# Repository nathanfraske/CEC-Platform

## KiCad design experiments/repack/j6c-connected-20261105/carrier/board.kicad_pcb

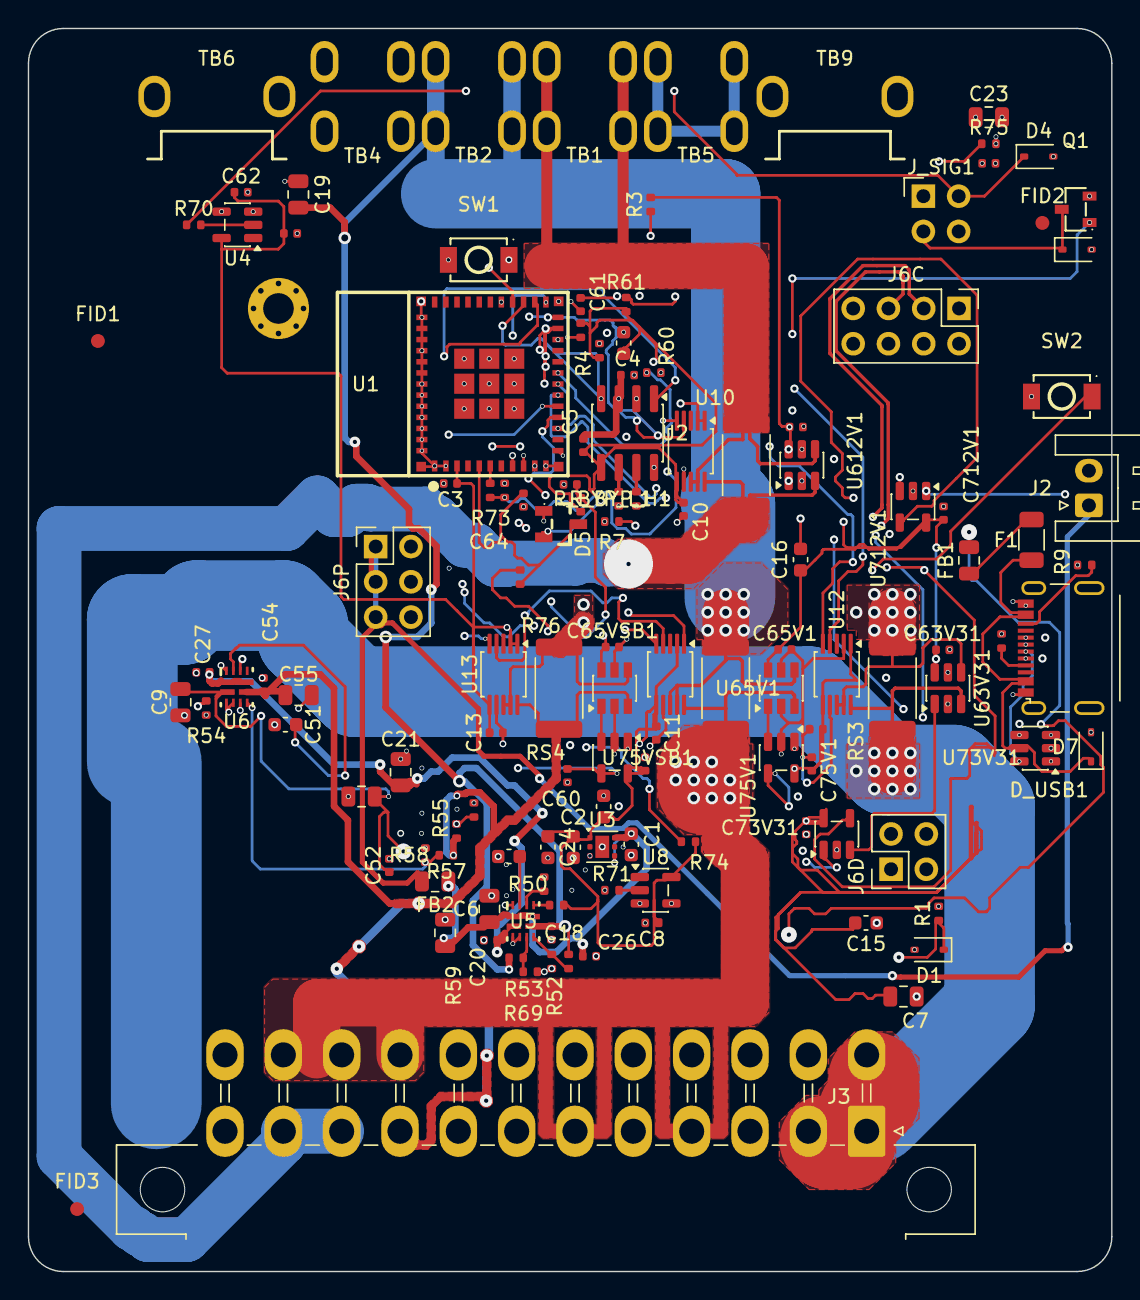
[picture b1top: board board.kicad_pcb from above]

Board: 6 copper layers, 78.0 x 89.5 mm, 129 parts (0 on the bottom side), 63 nets.

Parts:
C1, C2, C14, C15, C16, C17, C24: 1uF; C_0603_1608Metric
C3, C4, C5, C8, C10, C11, C12, C13, C18, C20, C22, C26, C27, C28, C52, C54, C60, C61, C62, C63, C63V31, C64, C65V1, C65VSB1, C73V31, C75V1, C75VSB1, C612V1, C712V1: 100nF; C_0402_1005Metric
C6, C7, C9, C19, C21, C23, C53, C55: 10uF; C_0805_2012Metric
C25: 22uF; C_0805_2012Metric
C50: 2u2; C_0603_1608Metric
C51: 2.2uF; C_0603_1608Metric
D1, D3, D4, D7: PESD5V0S1BA; D_SOD-323
D5: BAT54S; SOT-23-3_L2.9-W1.3-P1.90-LS2.4-TL
D_USB1: USBLC6-2SC6; SOT-23-6
F1: 750mA/16V PTC; R_1206_3216Metric
FB1: 600R@100MHz FB (MPZ2012S601AT000); C_0805_2012Metric
FB2: 0R (FB position, populate on EMC evidence); C_0805_2012Metric
FID1, FID2, FID3: Fiducial_1mm_Mask2mm
H1: M2 GND lug; MountingHole_2.2mm_M2_Pad_Via_Slim_6mm_Hardware
J2: TO-HUB-PWR; JST_XH_S2B-XH-A_1x02_P2.50mm_Horizontal
J3: ATX-24 PSU; Molex_Mini-Fit_Jr_5569-24A1_2x12_P4.20mm_Horizontal
J5: USB-C 2.0; USB_C_Receptacle_GCT_USB4215-03-A
J6C: TO-HUB-STACK-COMMS; PinHeader_2x04_P2.54mm_Vertical
J6D: TO-HUB-STACK-ID; PinHeader_2x02_P2.54mm_Vertical
J6P: TO-HUB-STACK-PWR; PinHeader_2x03_P2.54mm_Vertical
J_SIG1: SSQ-102-03-G-D; Samtec_SSQ-102-03-G-D_2x02_P2.54mm_Vertical
Q1: AO3400A; SOT-23-3_L2.9-W1.3-P1.90-LS2.4-BR
R1, R3, R4: 2.2kΩ; R_0402_1005Metric
R2, R10, R51, R56, R60, R61, R69, R76: 10kΩ; R_0402_1005Metric
R7, R52, R54, R57, R73, R75: 100kΩ; R_0402_1005Metric
R8, R9: 5.1kΩ; R_0402_1005Metric
R50: 20kΩ; R_0402_1005Metric
R53, R58: 33kΩ; R_0402_1005Metric
R55, R59: 43.2kΩ; R_0402_1005Metric
R70, R71: 1kΩ; R_0402_1005Metric
R72: 100Ω; R_0402_1005Metric
R74: 15kΩ; R_0402_1005Metric
RS1, RS2, RS3: 2mΩ; R_2512_6332Metric
RS4: R025; R_2512_6332Metric
R_BYP_H1: 0Ω; R_0402_1005Metric
R_BYP_L1: 0Ω; R_0402_1005Metric
SW1: BOOT; TS-1088-AR02016
SW2: RESET; TS-1088-AR02016
TB1, TB2, TB4, TB5: XFCN T34069; XFCN_T34069_THT_M3_40A
TB6, TB9: TTR32100127-0600; XFCN_TTR32100127-0600_THT_M3_60A
U1: ESP32-C6-MINI-1-N4; ESP32-C6-MINI-1
U2: TJA1051T/3; SOIC-8_3.9x4.9mm_P1.27mm
U3: TLV75533PDRVR; WSON-6-1EP_2x2mm_P0.65mm_EP1x1.6mm
U4, U8: 74LVC1G17; SOT-23-5
U5, U6: TPS2121RUXR; RUX0012A
U10, U11, U12, U13: INA238; VSSOP-10_3x3mm_P0.5mm
U63V31, U612V1: INA181A2IDBVR; SOT-23-6
U65V1, U65VSB1: INA181A2IDBVR; SOT-23-6_TI_DBV0006A
U73V31, U75V1, U75VSB1, U712V1: TLV7011DBVR; SOT-23-5

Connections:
+3V3: C2.1, C3.1, C7.1, C8.1, C10.1, C11.1, C12.1, C13.1, C14.1, C15.1, C16.1, C17.1, C24.1, C28.1, C62.1, C63.1, C63V31.1, C65V1.1, C65VSB1.1, C73V31.1, C75V1.1, C75VSB1.1, C612V1.1, C712V1.1, D5.2, R2.1, R3.2, R4.2, R10.1, R51.2, R61.1, R74.1, U1.3, U2.5, U3.1, U4.5, U8.5, U10.6, U11.2, U11.6, U12.1, U12.6, U13.1, U13.2, U13.6, U63V31.6, U65V1.6, U65VSB1.6, U73V31.5, U75V1.5, U75VSB1.5, U612V1.6, U712V1.5
+5VSB: C54.1, C55.1, J3.9, R55.1, R57.1, RS4.1, U6.7, U13.10, U65VSB1.3
+5V_MAIN: C18.1, C19.1, R52.1, R59.1, RS2.2, TB2.1, U5.7, U11.8, U11.9, U65V1.4
+5V_SYS: C1.1, C4.1, C6.1, C25.1, C26.1, C28.2, FB2.1, U2.3, U3.4, U3.6, U5.1, U5.8
/3V3 REGULATOR + MCU/EN: C5.1, R2.2, SW2.2, U1.8
/3V3 REGULATOR + MCU/IO8_STRAP: R10.2, U1.22
/5V SOURCE MUX + USB SERVICE INGRESS/5VSB_MUX: C20.1, C21.1, C27.1, U5.2, U6.1, U6.8
/5V SOURCE MUX + USB SERVICE INGRESS/ILIM: R50.1, U5.10
/5V SOURCE MUX + USB SERVICE INGRESS/MUX_ST: R51.1, U5.9
/5V SOURCE MUX + USB SERVICE INGRESS/PR1: R52.2, R53.1, U5.6
/5V SOURCE MUX + USB SERVICE INGRESS/SS: C50.1, U5.11
/5V SOURCE MUX + USB SERVICE INGRESS/U5_OV1: R59.2, R69.1, U5.5
/5V SOURCE MUX + USB SERVICE INGRESS/U6_ILM: R54.1, U6.10
/5V SOURCE MUX + USB SERVICE INGRESS/U6_OV1: R55.2, R56.1, U6.5
/5V SOURCE MUX + USB SERVICE INGRESS/U6_PR1: R57.2, R58.1, U6.6
/5V SOURCE MUX + USB SERVICE INGRESS/U6_SS: C51.1, U6.11
/5V SOURCE MUX + USB SERVICE INGRESS/USB_CC1: J5.A5, R8.1
/5V SOURCE MUX + USB SERVICE INGRESS/USB_CC2: J5.B5, R9.1
/5V SOURCE MUX + USB SERVICE INGRESS/VBUS: C9.1, C52.1, C53.1, FB1.2, U6.2
/5V SOURCE MUX + USB SERVICE INGRESS/VBUS_F: F1.2, FB1.1
/5V SOURCE MUX + USB SERVICE INGRESS/VBUS_RAW: D7.1, D_USB1.5, F1.1, J5.A4, J5.A9, J5.B4, J5.B9
/ATX INTERPOSER + CONTROL SIGNALS/ATX_NEG12V: C22.1, C23.1, J3.14, J_SIG1.1, R75.2
/ATX INTERPOSER + CONTROL SIGNALS/ATX_PSON: D3.1, J3.16, J_SIG1.2, Q1.3, R71.1
/ATX INTERPOSER + CONTROL SIGNALS/ATX_PWROK: D4.1, J3.8, J_SIG1.3, R70.1
/ATX INTERPOSER + CONTROL SIGNALS/NEG12V_DIV: R74.2, R75.1, R76.1
/ATX INTERPOSER + CONTROL SIGNALS/PSON_BUF: R71.2, U8.2
/ATX INTERPOSER + CONTROL SIGNALS/PSON_GATE: Q1.1, R72.2, R73.1
/ATX INTERPOSER + CONTROL SIGNALS/PWROK_BUF: R70.2, U4.2
/CAN_RX: U1.27, U2.4
/CAN_TX: U1.26, U2.1
/DET3V3: U1.15, U73V31.1
/DET5V: U1.29, U75V1.1
/DET5VSB: U1.16, U75VSB1.1
/DET12V: U1.28, U712V1.1
/DETECT_SENSE: R7.1, U1.12
/FOUR-RAIL PRECISION + FAST SENSING/DETAMP3V3: U63V31.1, U73V31.3
/FOUR-RAIL PRECISION + FAST SENSING/DETAMP5V: U65V1.1, U75V1.3
/FOUR-RAIL PRECISION + FAST SENSING/DETAMP5VSB: U65VSB1.1, U75VSB1.3
/FOUR-RAIL PRECISION + FAST SENSING/DETAMP12V: U612V1.1, U712V1.3
/FOUR-RAIL PRECISION + FAST SENSING/THRESH: C60.1, R60.2, U73V31.4, U75V1.4, U75VSB1.4, U712V1.4
/GPIO0: C61.1, R61.2, SW1.2, U1.23
/HUB LINK + CAN + STACK/+5V_SYS_PORT: FB2.2, J2.1, J6P.1, J6P.3, J6P.5
/HUB LINK + CAN + STACK/CAN_H: R_BYP_H1.2, U2.7
/HUB LINK + CAN + STACK/CAN_H_BUS: J6C.3, R_BYP_H1.1
/HUB LINK + CAN + STACK/CAN_L: R_BYP_L1.2, U2.6
/HUB LINK + CAN + STACK/CAN_L_BUS: J6C.5, R_BYP_L1.1
/HUB LINK + CAN + STACK/DETECT: D1.1, J6D.1, R1.1, R7.2
/I2C_SCL: R4.1, U1.25, U10.5, U11.5, U12.5, U13.5
/I2C_SDA: R3.1, U1.24, U10.4, U11.4, U12.4, U13.4
/NEG12V_ADC: C64.1, D5.3, R76.2, U1.5
/PSON_DRIVE: R72.1, U1.6
/PSON_SENSE: U1.10, U8.4
/PWROK_SENSE: U1.9, U4.4
/SENSE3V3_HI: J3.1, J3.2, J3.12, J3.13, RS3.1, U12.10, U63V31.3
/SENSE3V3_LO: RS3.2, TB4.1, U12.8, U12.9, U63V31.4
/SENSE5VSB_LO: RS4.2, TB5.1, U13.8, U13.9, U65VSB1.4
/SENSE5V_HI: J3.4, J3.6, J3.21, J3.22, J3.23, RS2.1, U11.10, U65V1.3
/SENSE12V_HI: J3.10, J3.11, RS1.1, U10.10, U612V1.3
/SENSE12V_LO: RS1.2, TB1.1, U10.8, U10.9, U612V1.4
/THRESH_PWM: R60.1, U1.19
/USB_D_N: D_USB1.3, D_USB1.4, J5.A7, J5.B7, U1.17
/USB_D_P: D_USB1.1, D_USB1.6, J5.A6, J5.B6, U1.18
GND: C1.2, C2.2, C3.2, C4.2, C5.2, C6.2, C7.2, C8.2, C9.2, C10.2, C11.2, C12.2, C13.2, C14.2, C15.2, C16.2, C17.2, C18.2, C19.2, C20.2, C21.2, C22.2, C23.2, C24.2, C25.2, C26.2, C27.2, C50.2, C51.2, C52.2, C53.2, C54.2, C55.2, C60.2, C61.2, C62.2, C63.2, C63V31.2, C64.2, C65V1.2, C65VSB1.2, C73V31.2, C75V1.2, C75VSB1.2, C612V1.2, C712V1.2, D1.2, D3.2, D4.2, D5.1, D7.2, D_USB1.2, H1.1, J2.2, J3.3, J3.5, J3.7, J3.15, J3.17, J3.18, J3.19, J3.24, J5.A1, J5.A12, J5.B1, J5.B12, J5.S1, J6C.1, J6C.2, J6C.7, J6C.8, J6D.2, J6D.4, J6P.2, J6P.4, J6P.6, J_SIG1.4, Q1.2, R1.2, R8.2, R9.2, R50.2, R53.2, R54.2, R56.2, R58.2, R69.2, R73.2, SW1.1, SW2.1, TB6.1, TB9.1, U1.1, U1.2, U1.11, U1.14, U1.36, U1.37, U1.38, U1.39, U1.40, U1.41, U1.42, U1.43, U1.44, U1.45, U1.46, U1.47, U1.48, U1.49, U1.50, U1.51, U1.52, U1.53, U2.2, U2.8, U3.3, U3.7, U4.3, U5.3, U5.4, U5.12, U6.3, U6.4, U6.12, U8.3, U10.1, U10.2, U10.7, U11.1, U11.7, U12.2, U12.7, U13.7, U63V31.2, U63V31.5, U65V1.2, U65V1.5, U65VSB1.2, U65VSB1.5, U73V31.2, U75V1.2, U75VSB1.2, U612V1.2, U612V1.5, U712V1.2

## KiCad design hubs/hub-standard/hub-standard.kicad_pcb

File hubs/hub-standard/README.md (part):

# Hub Standard

> **Historical alpha record.** The current BETA Hub is
> `beta/hub-standard-rev2`. Use `LAYOUT-GUIDE.md`,
> `docs/decisions/owner-session-2026-08-01.md`, and
> `docs/standard-tier-review/STANDARD-DESIGN-SHEET.md` for current rules. The
> four-layer layout and pre-fabrication claims below are not BETA release
> evidence.

Tier 1 of 4. The mainstream Hub: 4 ports, classical CAN, USB Full Speed.
Canonical detail in spec [§4](../../CEC-Platform-Ground-Truth-Spec.md). All
v1.1 decisions carry forward unchanged **except connector and cabling**.

| Item | Decision |
|---|---|
| Tier | 1 of 4 |
| MCU | ESP32-S3-WROOM-1-N16R8 (16 MB flash + 8 MB PSRAM). MINI-1 has no 16 MB SKU, so the aggregation Hub uses WROOM; modules stay on MINI-1. Wireless functions are disabled across the BETA family. |
| Ports | 4× RJ-45 8P8C, locking boot (was Mini-Fit Jr 12-circuit) |
| Protocol | Classical CAN @ 500 kbps over the TJA1051T/3 (classical, VIO 3.3 V) |
| Termination | Fixed 120 Ω split at the Hub |
| Host link | USB Full Speed |
| Bulk power | Dedicated 2-pin +5VSB power-in from the 24-pin module; distributes to the 4 ports over RJ-45 VCC (§2.7, OQ-1 locked) |
| RS-485 | **Not populated** (Standard); pair 2 unused, terminated at the module side |
| Regulator | LP5907 LDO |
| Hold-up | 4700 µF / 16 V aluminum electrolytic on the isolated `+5V_HOLD` node (Panasonic EEVFK1C472M, LCSC C401967, CP_Elec_16x17.5). Chemistry corrected "polymer" → electrolytic, **ratified spec v1.9** (4700 µF polymer is unobtainable; electrolytic is right for a diode-isolated reservoir feeding the LDO). |
| Surge cap | 470 µF on the shared `+5VSB` distribution rail (rides out module load-steps; LCSC C116423, CP_Elec_6.3x7.7) |
| Inrush | TPS2121 mux soft-start (`C_SS` = 2.2 µF) — **supersedes** the v1.1 discrete 1 Ω 1 W series resistor (the mux ramps the bulk-cap charge). Spec reconciled 2026-06-04. |
| Reverse polarity / isolation | TPS2121 OR-mux blocks reverse current on the source side; **D1** Schottky isolates the `+5V_HOLD` reservoir downstream. D1 is **SB120** (1 A / 20 V) as built; **SS14** (1 A / 40 V) is a drop-in higher-margin alternative — both adequate on the 5 V rail. |
| Supervisor | TPS3839K33 (3.3V-rail brownout/POR), RESET → ESP32 EN |
| Storage / identity | ESP32-S3-WROOM-1 internal 16 MB flash + 8 MB PSRAM; factory MAC + database (no eFuse, no secure element) |
| LEDs | 7× SK6812 MINI-E RGB chain, firmware current cap (§2.5 / OQ-2). Data line 3.3 → 5 V level-shifted: **U6 (SN74AHCT1G08**, both inputs tied = AHCT buffer; VCC = +5VSB, C14 100 nF decap) + **R14** 330 Ω series into DL1.DIN — the ESP32's 3.3 V GPIO is below the 5 V SK6812 V_IH (0.7·VDD ≈ 3.5 V), so the buffer guarantees a clean 5 V data high with no LED dimming. (74AHCT1G34 was the first pick but isn't on JLCPCB; the 1G08-as-buffer is the stocked equivalent in the same SOT-23-5 land.) |
| Service button | Hidden, GPIO0 (download mode) |
| NanoKVM aux link (J7) | 5-pin **right-angle** JST-PH (**S5B-PH-K-S**, **C157923** — side-entry so the external NanoKVM cable exits a board edge; was the top-entry B5B-PH-K-S, changed v3.9 right-angle correction), spec v3.7 / OQ-51 (v3.9 connector). Pins: UART TX/RX (ESP32 IO11/IO12 through 33 Ω series **R19/R20**, C25105), the shared **+5VSB** rail (§2.9), GND, and the NanoKVM's 3.3 V reference. **No trigger GPIO** — triggers ride the UART in-band. The 3.3 V line is **untrusted**: it is read for presence + health, never as a reference. **Compensation** — the KVM 3V3 is divided 47k/10k (**R21/R22**, C25792/C25744) into ADC1 **IO1**, and the Hub's own LDO **+3V3** is divided by an identical 47k/10k (**R23/R24**) into ADC1 **IO2**; firmware takes the *ratio* so the ADC and divider error cancel and a drifted/sagging KVM rail is detected, not believed. Low-cap ESD **D7** (PESD5V0S1BA, C5261083) clamps the cabled ref pin. |
| Mounting | 4× M3 corner holes, chassis-grounded (`cec-MountingHole:MountingHole_3.2mm_M3_Pad_Via` — pad + stitching vias to the In1 GND plane; PC-standard fastener, spec v1.10) |
| Board temperature | 1× NTC divider into ADC1 **IO3**: **TH1** (`cec-vendor:Thermistor_NTC`, Murata **NCP15XH103F03RC**, 10 kΩ, C77131) on the high side from **+3V3**, **R25** 10 kΩ fixed (C25744) to GND, **C16** 100 nF filter on the node. Placed near the §2.9 front-end (the warmest area). Gives the always-on Hub a board-temp/ambient datum for Concierge and a thermal watch on the subsystem-power path (LED/load throttle, OQ-2). Same topology as the 12VHPWR TH1/TH2, using the repo-vendored generic NTC. |
| PCB | 4-layer 1.6 mm, ENIG, matte black |
| BOM target | ~$36 (100-qty) |

## 24-pin dual-feed — Hub-side workaround options

The 24-pin module is both the bulk 5VSB source (JST) and a module on a port, so
its RJ-45 VCC can parallel the JST feed (spec §2.7 v3.3). The clean fix is at the
source (24-pin rev3: RJ-45 VCC no-connect), and for the prototype the rev2
bring-up mitigations apply. If you want the **Hub** robust against any
source-module regardless of its wiring, options in order of cost:

1. **Move port VCC distribution to the mux *input* (pre-mux, `5VSB_RAW`).** Ties
   the RJ-45 VCC and the JST to the same node, so the mux is no longer bypassed
   (kills the mux-defeat and the USB-only back-feed). Doesn't remove the cable-R
   current split, but preserves mux integrity. Zero added parts; caveat: ports
   aren't powered on USB-only bench (fine — no modules attached then).
2. **Per-port OR-ing diode on VCC** (Hub→port). A low-drop Schottky (or ideal-
   diode IC) in series with each port's VCC lets the Hub feed modules but blocks
   any module back-feeding the Hub — eliminates the parallel path for any
   source-module. Cost: ~0.3–0.4 V drop on module VCC (LP5907 / SK6812 tolerate
   ~4.6 V), or a small ideal-diode IC for near-zero drop.
3. **Diode on one designated power-source port only.** If the 24-pin always lands
   on a fixed port, block only that port — no drop on the other three. Trades
   any-port flexibility for that port.

Recommendation: rely on the 24-pin rev3 source fix; the Hub diode is insurance.
The current prototype Hub needs no change if the rev2 bring-up mitigation is used.

## Open questions touching this board

- **OQ-1 (locked 2026-05-30):** the Hub takes bulk 5VSB on a dedicated 2-pin
  power-in connector from the 24-pin module and distributes 5VSB to its 4 ports
  over RJ-45 VCC (spec §2.7). The single-pin trunk concern is resolved.
- **OQ-2:** firmware LED current cap value / max LED state to budget.

## Status

> **Status (2026-06-04 — schematic complete + ERC-clean; PCB placed and fully
> routed (DRC: 0 unconnected), in pre-fab review. The `DRAFT` marker still
> skips CI ERC/DRC.):** RJ-45 re-cut COMPLETE (4 ports + the 2-pin
> `CEC_PWR_IN_2P` 5VSB power-in). MCU is **ESP32-S3-WROOM-1-N16R8** (symbol +
> footprint vendored, with the controller placed at the board edge).
> 5VSB front-end built: TPS2121 mux (PSU/USB OR-in) → **D1** isolation Schottky
> → 4700 µF hold-up on the isolated `+5V_HOLD` node → LP5907; 470 µF `C_bulk`
> surge cap on the shared `+5VSB`; blackout-sense divider → GPIO8. **ERC: 0
> errors.** USB ESD (D6) + per-port DETECT ESD (D2–D5) populated; J2–J5 on the
> FTP shielded footprint.
>
> **Pre-fab review (2026-06-04):** found and fixed the netclass-pattern bug
> (Power/CAN/USB patterns lacked the `/` prefix → rail nets fell into Default,
> so DRC was blind to under-width power traces). With it fixed DRC now reports
> the real punch-list:
> - **38 `track_width` errors** on the power nets — the 5VSB trunk (`/5VSB_RAW`,
>   0.4 mm) needs a pour or ≥1.5 mm; `/USB_VBUS` and `/+5V_HOLD` need ≥0.5 mm.
> - **Ground/return-path:** only In1 is poured and it reads as fragmented
>   (likely stale fill — `kicad-cli` can't refill). **Refill zones in the GUI
>   (`B`) first**, confirm In1 is one island, then widen/pour the 5VSB trunk on
>   F.Cu. CAN (CAN_H/L) and USB (D±) are 100 % on F.Cu over In1, 0 vias — good.
>   The slow/don't-care lines (DETECT/LED/GPIO/EN) ride In2 under In1 — also OK.
>   Power (+5VSB/+3V3/USB_VBUS) is currently long thin traces on **B.Cu**; move
>   it to a F.Cu pour (LAYOUT-GUIDE §"Power routing").
> - **CAN_RX/CAN_L** routed ~0.03–0.13 mm from the board edge — pull in.
> - Tent the via-in-pad on **C1** (4700 µF); add a 2nd GND via at **D6**; silk
>   cleanup on the RJ-45 shield pads + board-edge silk.
>
> Netclasses (Power/USB/CAN — patterns fixed), the `.kicad_dru`, and
> `LAYOUT-GUIDE.md` are in. 4-layer 1.6 mm, In1 = GND plane (EMC — see
> LAYOUT-GUIDE.md). Remaining before fab: the GUI pour/route pass above, then
> drop the `DRAFT` marker.
>
> **Update (2026-06-05):** the GUI pour/route pass above is largely DONE — In1
> refilled to **one solid island**, `+5VSB` widened to 1.0 mm, and the
> `/5VSB_RAW` trunk taken to a fat trace. **DRC: 0 `track_width`, 0 unconnected**
> (remaining is silk cosmetics + one stray `/USB_VBUS` stub to delete). **SK6812
> data level shifter ADDED** (U6 SN74AHCT1G08 AND-as-buffer + R14 330 Ω + C14
> 100 nF; ERC + netlist verified: ESP LED-data GPIO IO25 → U6 → R14 → DL1.DIN,
> VCC on +5VSB).
>
> **BOM now fully sourced for JLCPCB assembly** (2026-06-05): every one of the 33
> lines carries an LCSC part (15 Basic/Preferred, 18 Extended; ~$12.11/board in
> parts, ESP32 = $5.15 of it). Files in `bom/`: `bom.csv` (tracking) and
> `hub-standard-BOM-jlcpcb.csv` (Comment/Designator/Footprint/LCSC upload). Part
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
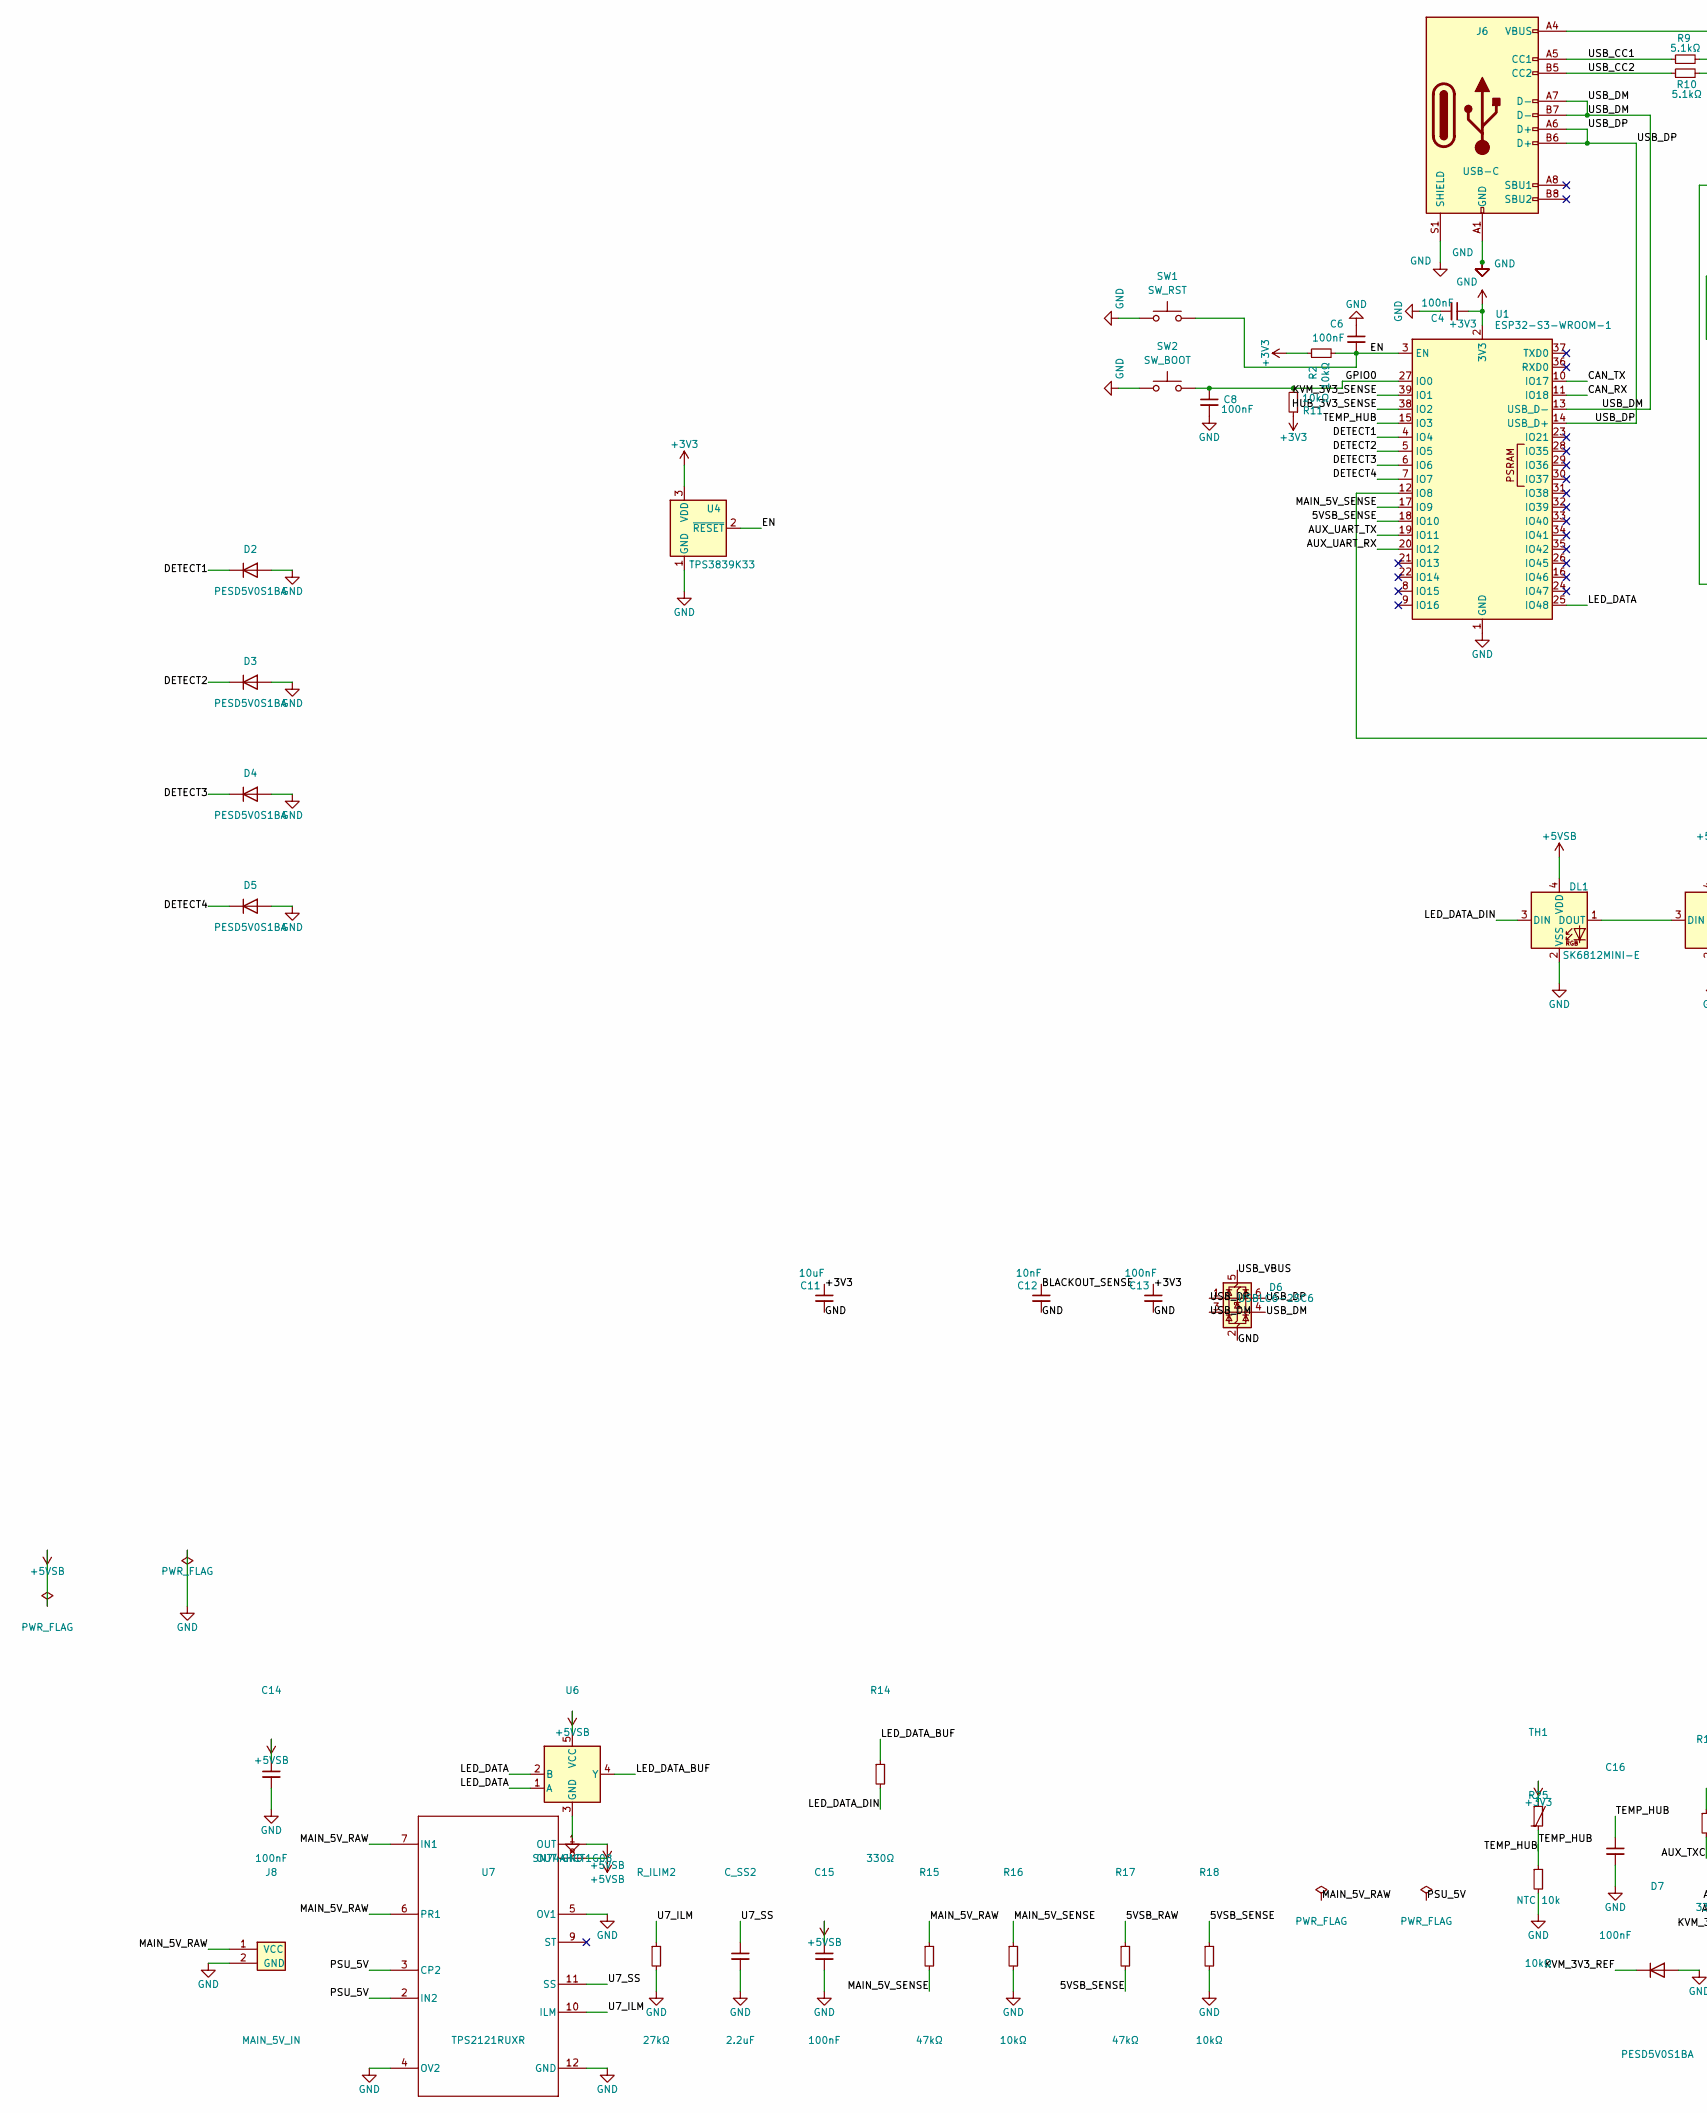
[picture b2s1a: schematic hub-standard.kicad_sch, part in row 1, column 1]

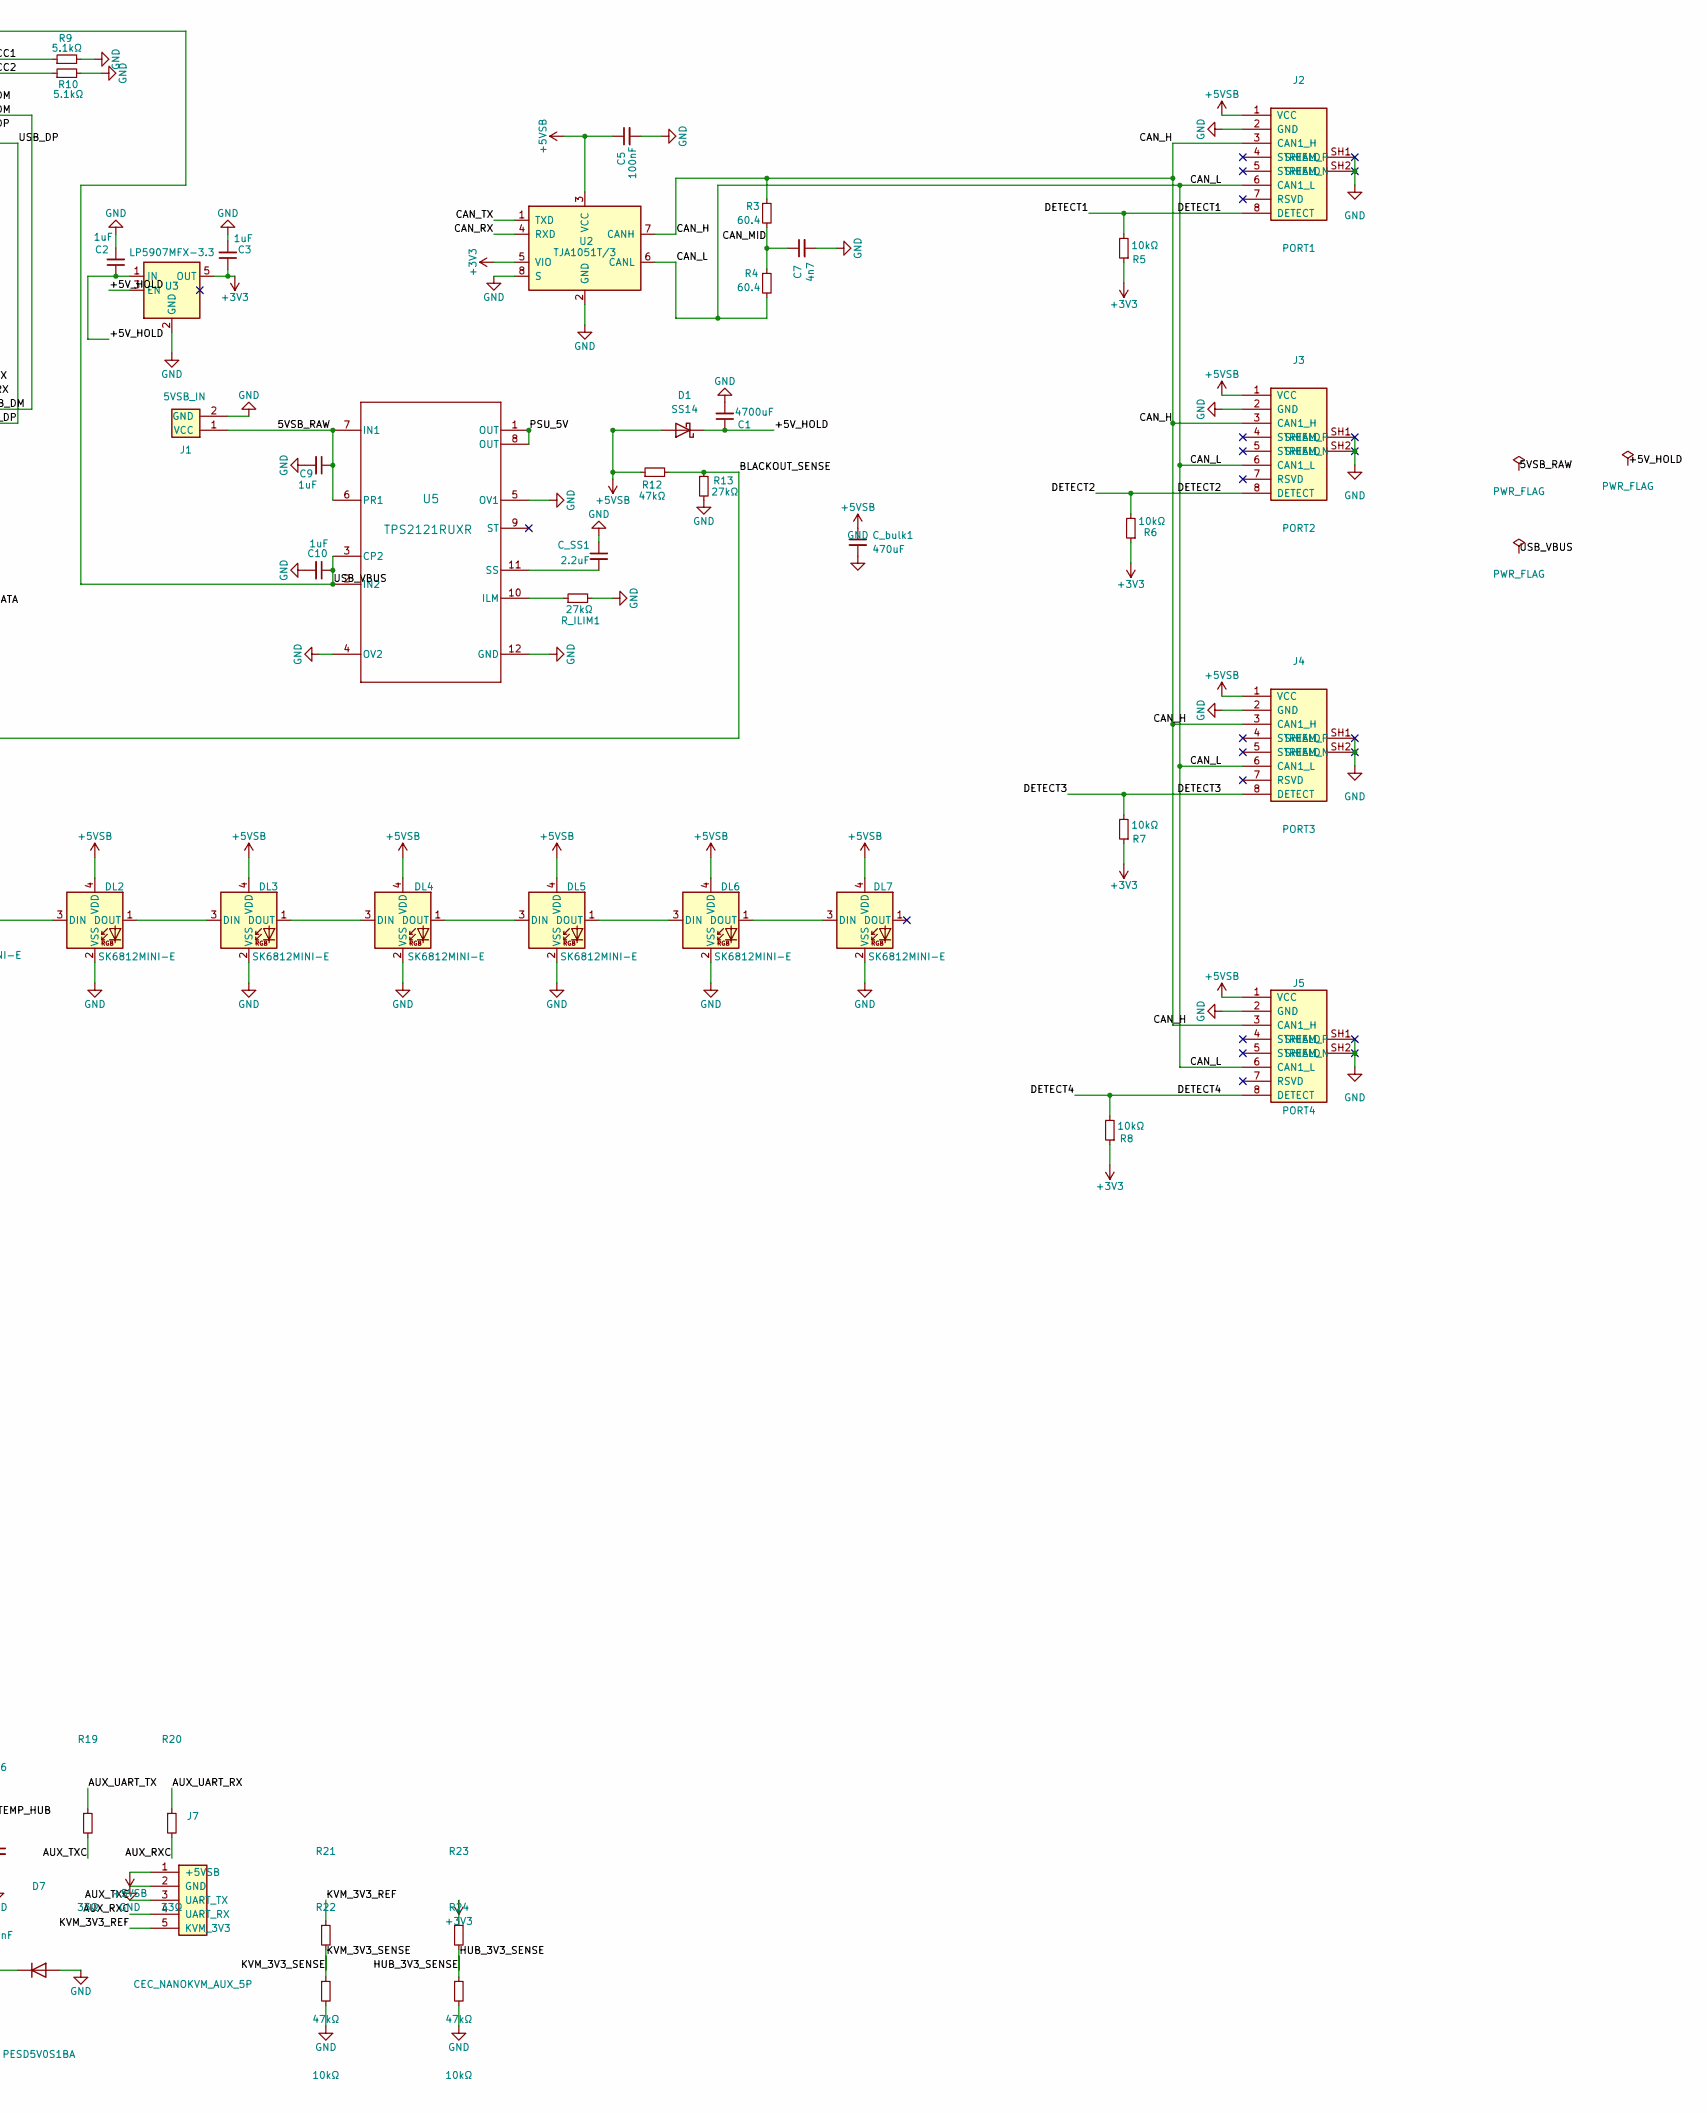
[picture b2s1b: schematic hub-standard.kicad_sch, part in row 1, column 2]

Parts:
C1: 4700uF; CP_Elec_16x17.5; MPN VKMI2101C472MV; LCSC C487318
C2, C3, C9, C10: 1uF; C_0603_1608Metric; MPN CL10A105KB8NNNC; LCSC C15849
C4, C5, C6, C8, C14, C15, C16: 100nF; C_0402_1005Metric; MPN CL05B104KO5NNNC; LCSC C1525
C7: 4n7; C_0402_1005Metric; MPN 0402B472K500NT; LCSC C1538
C11: 10uF; C_0603_1608Metric; MPN CL10A106MA8NRNC; LCSC C96446
C12: 10nF; C_0402_1005Metric; MPN CL05B103KB5NNNC; LCSC C15195
C13: 100nF; C_0603_1608Metric; MPN CC0603KRX7R9BB104; LCSC C14663
C_SS1, C_SS2: 2.2uF; C_0603_1608Metric; MPN CL10A225KO8NNNC; LCSC C23630
C_bulk1: 470uF; CP_Elec_6.3x7.7; MPN RVT1A471M0607; LCSC C335982
D1: SS14; D_SMA; MPN SS14; LCSC C2480
D2, D3, D4, D5, D7: PESD5V0S1BA; D_SOD-323; MPN PESD5V0S1BA; LCSC C5261083
D6: USBLC6-2SC6; SOT-23-6; MPN USBLC6-2SC6; LCSC C2687116
DL1, DL2, DL3, DL4, DL5, DL6, DL7: SK6812MINI-E; LED_SK6812MINI_PLCC4_3.5x3.5mm_P1.75mm; MPN SK6812MINI-E; LCSC C5149201
J1: 5VSB_IN; JST_XH_S2B-XH-A_1x02_P2.50mm_Horizontal; MPN S2B-XH-A(LF)(SN); LCSC C157931
J2: PORT1; RJ45_FTP_Shielded_Horizontal; MPN KH-RJ45-58-8P8C; LCSC C2683360
J3: PORT2; RJ45_FTP_Shielded_Horizontal; MPN KH-RJ45-58-8P8C; LCSC C2683360
J4: PORT3; RJ45_FTP_Shielded_Horizontal; MPN KH-RJ45-58-8P8C; LCSC C2683360
J5: PORT4; RJ45_FTP_Shielded_Horizontal; MPN KH-RJ45-58-8P8C; LCSC C2683360
J6: USB-C; USB_C_Receptacle_XKB_U262-16XN-4BVC11; MPN U262-16XN-4BVC11; LCSC C2765186
J7: CEC_NANOKVM_AUX_5P; JST_PH_S5B-PH-K-S_1x05_P2.00mm_Horizontal; MPN S5B-PH-K-S(LF)(SN); LCSC C157923
J8: MAIN_5V_IN; JST_XH_S2B-XH-A_1x02_P2.50mm_Horizontal; MPN S2B-XH-A(LF)(SN); LCSC C157931
R2, R5, R6, R7, R8, R11, R16, R18, R22, R24, R25: 10kΩ; R_0402_1005Metric; MPN 0402WGF1002TCE; LCSC C25744
R3, R4: 60.4; R_0402_1005Metric; MPN GR0402F60R4TAG00; LCSC C49654185
R9, R10: 5.1kΩ; R_0402_1005Metric; MPN 0402WGF5101TCE; LCSC C25905
R12, R15, R17, R21, R23: 47kΩ; R_0402_1005Metric; MPN 0402WGF4702TCE; LCSC C25792
R13: 27kΩ; R_0402_1005Metric; MPN 0402WGF2702TCE; LCSC C25771
R14: 330Ω; R_0402_1005Metric; MPN 0402WGF3300TCE; LCSC C25104
R19, R20: 33Ω; R_0402_1005Metric; MPN 0402WGF330JTCE; LCSC C25105
R_ILIM1, R_ILIM2: 27kΩ; R_0402_1005Metric; MPN 0402WGF2702TCE; LCSC C25771
SW1: SW_RST; TS-1088-AR02016; MPN TS-1088-AR02016; LCSC C720477
SW2: SW_BOOT; TS-1088-AR02016; MPN TS-1088-AR02016; LCSC C720477
TH1: NTC 10k; NTC_0402_1005Metric; MPN NCP15XH103F03RC; LCSC C77131
U1: ESP32-S3-WROOM-1; MPN ESP32-S3-WROOM-1-N16R8; LCSC C2913202
U2: TJA1051T/3; SOIC-8_3.9x4.9mm_P1.27mm; MPN TJA1051T/3; LCSC C38695
U3: LP5907MFX-3.3; SOT-23-5; MPN LP5907MFX-3.3/NOPB; LCSC C80670
U4: TPS3839K33; SOT-23; MPN TPS3839K33DBZR; LCSC C96333
U5, U7: TPS2121RUXR; RUX0012A; MPN TPS2121RUXR; LCSC C485916
U6: SN74AHCT1G08; SOT-23-5; MPN SN74AHCT1G08DBVR; LCSC C113521

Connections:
+3V3: C3.1, C4.1, C11.1, C13.1, R2.1, R5.1, R6.1, R7.1, R8.1, R11.1, R23.1, TH1.1, U1.2 (3V3), U2.5 (VIO), U3.5 (OUT), U4.3 (VDD); also elsewhere on the board
+5VSB: C5.1, C14.1, C15.1, C_bulk1.1, D1.2 (A), DL1.4 (VDD), DL2.4 (VDD), DL3.4 (VDD), DL4.4 (VDD), DL5.4 (VDD), DL6.4 (VDD), DL7.4 (VDD), J2.1 (VCC), J3.1 (VCC), J4.1 (VCC), J5.1 (VCC), J7.1 (+5VSB), R12.1, U2.3 (VCC), U6.5 (VCC), U7.1 (OUT), U7.8 (OUT); also elsewhere on the board
/5VSB_RAW: C9.1, J1.1 (VCC), R17.1, U5.6 (PR1), U5.7 (IN1)
/5VSB_SENSE: R17.2, R18.1, U1.18 (IO10)
/+5V_HOLD: C1.1, C2.1, D1.1 (K), U3.1 (IN), U3.3 (EN); also elsewhere on the board
/AUX_RXC: J7.4 (UART_RX), R20.2
/AUX_TXC: J7.3 (UART_TX), R19.2
/AUX_UART_RX: R20.1, U1.20 (IO12)
/AUX_UART_TX: R19.1, U1.19 (IO11)
/BLACKOUT_SENSE: C12.1, R12.2, R13.1, U1.12 (IO8); also elsewhere on the board
/CAN_H: J2.3 (CAN1_H), J3.3 (CAN1_H), J4.3 (CAN1_H), J5.3 (CAN1_H), R3.1, U2.7 (CANH)
/CAN_L: J2.6 (CAN1_L), J3.6 (CAN1_L), J4.6 (CAN1_L), J5.6 (CAN1_L), R4.2, U2.6 (CANL)
/CAN_MID: C7.1, R3.2, R4.1
/CAN_RX: U1.11 (IO18), U2.4 (RXD)
/CAN_TX: U1.10 (IO17), U2.1 (TXD)
/DETECT1: D2.1 (K), J2.8 (DETECT), R5.2, U1.4 (IO4)
/DETECT2: D3.1 (K), J3.8 (DETECT), R6.2, U1.5 (IO5)
/DETECT3: D4.1 (K), J4.8 (DETECT), R7.2, U1.6 (IO6)
/DETECT4: D5.1 (K), J5.8 (DETECT), R8.2, U1.7 (IO7)
/EN: C6.2, R2.2, SW1.2, U1.3 (EN), U4.2 (~RESET); also elsewhere on the board
/GPIO0: C8.1, R11.2, SW2.2, U1.27 (IO0); also elsewhere on the board
/HUB_3V3_SENSE: R23.2, R24.1, U1.38 (IO2)
/KVM_3V3_REF: D7.1 (K), J7.5 (KVM_3V3), R21.1
/KVM_3V3_SENSE: R21.2, R22.1, U1.39 (IO1)
/LED_DATA: U1.25 (IO48), U6.1 (A), U6.2 (B)
/LED_DATA_BUF: R14.1, U6.4 (Y)
/LED_DATA_DIN: DL1.3 (DIN), R14.2
/MAIN_5V_RAW: J8.1 (VCC), R15.1, U7.6 (PR1), U7.7 (IN1)
/MAIN_5V_SENSE: R15.2, R16.1, U1.17 (IO9)
/PSU_5V: U5.1 (OUT), U5.8 (OUT), U7.2 (IN2), U7.3 (CP2)
/TEMP_HUB: C16.1, R25.1, TH1.2, U1.15 (IO3)
/U7_ILM: R_ILIM2.1, U7.10 (ILM)
/U7_SS: C_SS2.1, U7.11 (SS)
/USB_CC1: J6.A5 (CC1), R9.1
/USB_CC2: J6.B5 (CC2), R10.1
/USB_DM: D6.3 (I/O2), D6.4 (I/O2), J6.A7 (D-), J6.B7 (D-), U1.13 (USB_D-)
/USB_DP: D6.1 (I/O1), D6.6 (I/O1), J6.A6 (D+), J6.B6 (D+), U1.14 (USB_D+)
/USB_VBUS: C10.1, D6.5 (VBUS), J6.A4 (VBUS), J6.A9 (VBUS), J6.B4 (VBUS), J6.B9 (VBUS), U5.2 (IN2), U5.3 (CP2); also elsewhere on the board
GND: C1.2, C2.2, C3.2, C4.2, C5.2, C6.1, C7.2, C8.2, C9.2, C10.2, C11.2, C12.2, C13.2, C14.2, C15.2, C16.2, C_SS1.1, C_SS2.2, C_bulk1.2, D2.2 (A), D3.2 (A), D4.2 (A), D5.2 (A), D6.2 (GND), D7.2 (A), DL1.2 (VSS), DL2.2 (VSS), DL3.2 (VSS), DL4.2 (VSS), DL5.2 (VSS), DL6.2 (VSS), DL7.2 (VSS), J1.2 (GND), J2.2 (GND), J2.SH1 (SHIELD), J2.SH2 (SHIELD), J3.2 (GND), J3.SH1 (SHIELD), J3.SH2 (SHIELD), J4.2 (GND), J4.SH1 (SHIELD), J4.SH2 (SHIELD), J5.2 (GND), J5.SH1 (SHIELD), J5.SH2 (SHIELD), J6.A1 (GND), J6.A12 (GND), J6.B1 (GND), J6.B12 (GND), J6.S1 (SHIELD), J7.2 (GND), J8.2 (GND), R9.2, R10.2, R13.2, R16.2, R18.2, R22.2, R24.2, R25.2, R_ILIM1.2, R_ILIM2.2, SW1.1, SW2.1, U1.1 (GND), U1.40 (GND), U1.41 (GND), U2.2 (GND), U2.8 (S), U3.2 (GND), U4.1 (GND), U5.4 (OV2), U5.5 (OV1), U5.12 (GND), U6.3 (GND), U7.4 (OV2), U7.5 (OV1), U7.12 (GND); also elsewhere on the board
unnamed: DL1.1 (DOUT), DL2.3 (DIN)
unnamed: DL2.1 (DOUT), DL3.3 (DIN)
unnamed: DL3.1 (DOUT), DL4.3 (DIN)
unnamed: DL4.1 (DOUT), DL5.3 (DIN)
unnamed: DL5.1 (DOUT), DL6.3 (DIN)
unnamed: DL6.1 (DOUT), DL7.3 (DIN)
unnamed: R_ILIM1.1, U5.10 (ILM)
unnamed: C_SS1.2, U5.11 (SS)

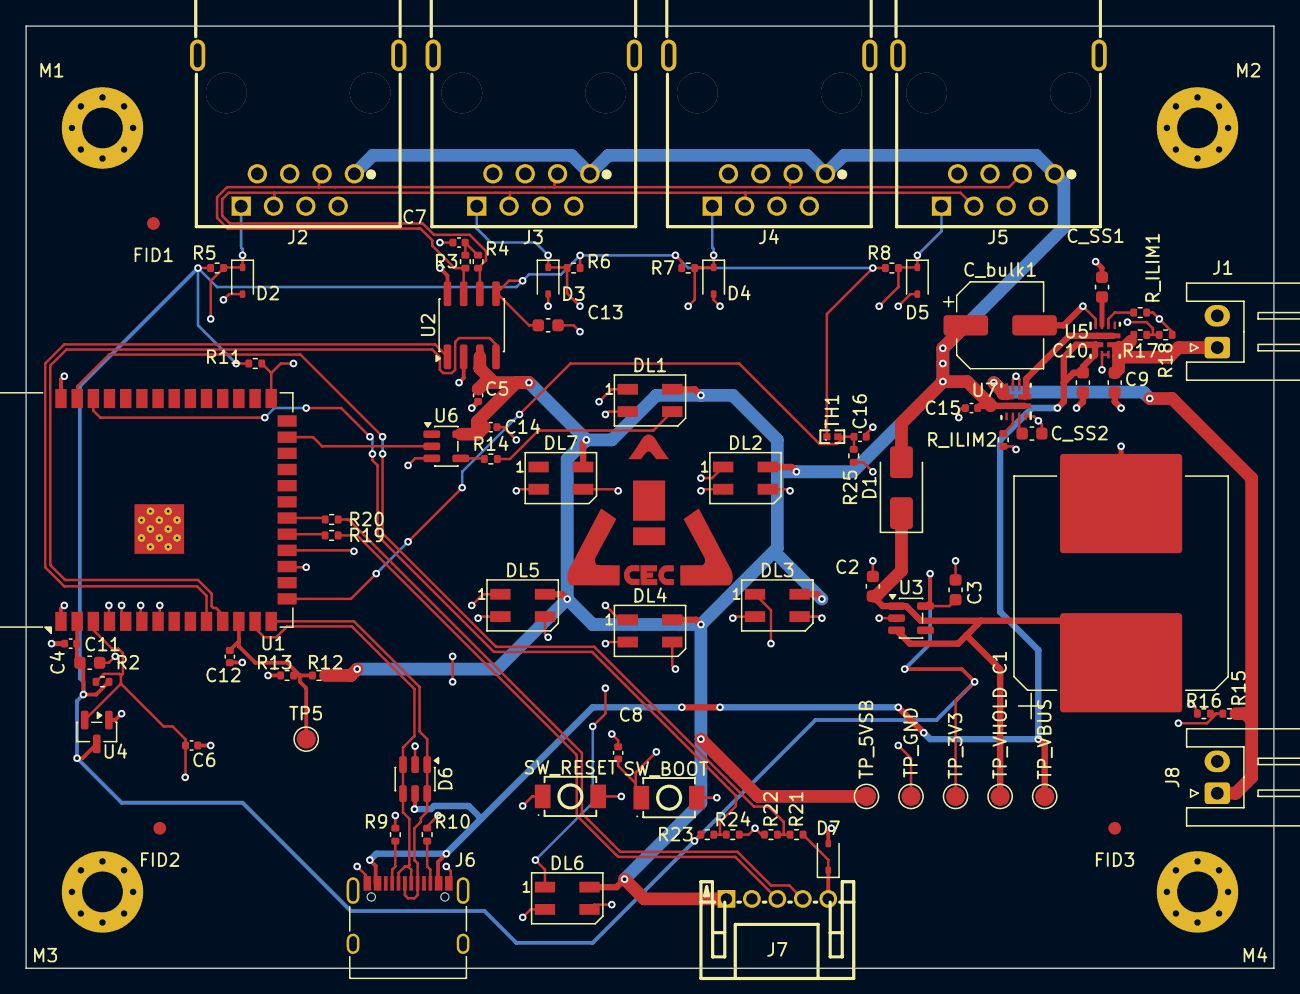
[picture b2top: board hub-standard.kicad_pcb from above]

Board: 4 copper layers, 98.0 x 74.0 mm, 91 parts (0 on the bottom side), 47 nets.

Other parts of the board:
FID1, FID2, FID3: Fiducial_1mm_Mask2mm
LOGO1: CEC_Logo_Copper
M1, M2, M3, M4: M3 Mount; MountingHole_3.2mm_M3_Pad_Via
SW_BOOT: SW_BOOT; TS-1088-AR02016
SW_RESET: SW_RST; TS-1088-AR02016
TP5: BLACKOUT; TestPoint_Pad_D1.5mm
TP_3V3: 3V3; TestPoint_Pad_D1.5mm
TP_5VSB: 5VSB; TestPoint_Pad_D1.5mm
TP_GND: GND; TestPoint_Pad_D1.5mm
TP_VBUS: USB_VBUS; TestPoint_Pad_D1.5mm
TP_VHOLD: 5V_HOLD; TestPoint_Pad_D1.5mm

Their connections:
+3V3: TP_3V3.1; also elsewhere on the board
+5VSB: TP_5VSB.1; also elsewhere on the board
/+5V_HOLD: TP_VHOLD.1; also elsewhere on the board
/BLACKOUT_SENSE: TP5.1; also elsewhere on the board
/EN: SW_RESET.2; also elsewhere on the board
/GPIO0: SW_BOOT.2; also elsewhere on the board
/USB_VBUS: TP_VBUS.1; also elsewhere on the board
GND: M1.1, M2.1, M3.1, M4.1, SW_BOOT.1, SW_RESET.1, TP_GND.1; also elsewhere on the board

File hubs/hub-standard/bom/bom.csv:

Reference,Qty,Value,Footprint,MPN,Manufacturer,LCSC,LC_Stock,Chosen_Distributor,Datasheet,Validated,DNP,Notes
C1,1,4700uF,CP_Elec_16x17.5,VKMI2101C472MV,Samxon,C487318,,,,,,
"C2,C3,C10,C9",4,1uF,0603,CL10A105KB8NNNC,Samsung,C15849,,,,,,
"C5,C4,C8,C6,C14,C15",6,100nF,0402,CL05B104KO5NNNC,Samsung,C1525,,,,,,
C7,1,4n7,0402,0402B472K500NT,Fenghua,C1538,,,,,,
C11,1,10uF,0603,CL10A106MA8NRNC,Samsung,C96446,,,,,,
C12,1,10nF,0402,CL05B103KB5NNNC,Samsung,C15195,,,,,,
C13,1,100nF,0603,CC0603KRX7R9BB104,YAGEO,C14663,,,,,,
"C_SS1,C_SS2",2,2.2uF,0603,CL10A225KO8NNNC,Samsung,C23630,,,,,,
C_bulk1,1,470uF,CP_Elec_6.3x7.7,RVT1A471M0607,Lelon,C335982,,,,,,
D1,1,SS14,SMA,SS14,MDD,C2480,,,http://www.diodes.com/_files/datasheets/ds23022.pdf,,,
"D2,D5,D3,D4",4,PESD5V0S1BA,SOD-323,PESD5V0S1BA,Nexperia,C5261083,,,,,,
D6,1,USBLC6-2SC6,SOT-23-6,USBLC6-2SC6,UMW,C2687116,,,,,,
"DL1,DL2,DL7,DL6,DL5,DL4,DL3",7,SK6812MINI-E,LED_SK6812MINI_PLCC4_3.5x3.5mm_P1.75mm,SK6812MINI-E,Opsco,C5149201,,,,,,
J1,1,5VSB_IN,JST_XH_S2B-XH-A_1x02_P2.50mm_Horizontal,S2B-XH-A(LF)(SN),JST,C157931,,,,,,
J2,1,PORT1,RJ45_FTP_Shielded_Horizontal,KH-RJ45-58-8P8C,Kinghelm,C2683360,,,,,,
J3,1,PORT2,RJ45_FTP_Shielded_Horizontal,KH-RJ45-58-8P8C,Kinghelm,C2683360,,,,,,
J4,1,PORT3,RJ45_FTP_Shielded_Horizontal,KH-RJ45-58-8P8C,Kinghelm,C2683360,,,,,,
J5,1,PORT4,RJ45_FTP_Shielded_Horizontal,KH-RJ45-58-8P8C,Kinghelm,C2683360,,,,,,
J6,1,USB-C,USB_C_Receptacle_XKB_U262-16XN-4BVC11,U262-16XN-4BVC11,XKB,C2765186,,,,,,
J8,1,MAIN_5V_IN,JST_XH_S2B-XH-A_1x02_P2.50mm_Horizontal,S2B-XH-A(LF)(SN),JST,C157931,,,,,,
"R4,R3",2,60.4,0402,GR0402F60R4TAG00,Viking,C49654185,,,,,,
"R8,R5,R2,R6,R7,R11,R16,R18",8,10kΩ,0402,0402WGF1002TCE,UNI-ROYAL,C25744,,,,,,
"R9,R10",2,5.1kΩ,0402,0402WGF5101TCE,UNI-ROYAL,C25905,,,,,,
"R12,R15,R17",3,47kΩ,0402,0402WGF4702TCE,UNI-ROYAL,C25792,,,,,,
R14,1,330Ω,0402,0402WGF3300TCE,UNI-ROYAL,C25104,,,,,,
"R_ILIM1,R13,R_ILIM2",3,27kΩ,0402,0402WGF2702TCE,UNI-ROYAL,C25771,,,,,,
SW1,1,SW_RST,TS-1088-AR02016,TS-1088-AR02016,XKB,C720477,,,,,,
SW2,1,SW_BOOT,TS-1088-AR02016,TS-1088-AR02016,XKB,C720477,,,,,,
U1,1,ESP32-S3-WROOM-1,ESP32-S3-WROOM-1,ESP32-S3-WROOM-1-N16R8,Espressif,C2913202,,,https://www.espressif.com/sites/default/files/documentation/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,,,
U2,1,TJA1051T/3,SOIC-8_3.9x4.9mm_P1.27mm,TJA1051T/3,NXP,C38695,,,,,,
U3,1,LP5907MFX-3.3,SOT-23-5,LP5907MFX-3.3/NOPB,Texas Instruments,C80670,,,,,,
U4,1,TPS3839K33,SOT-23,TPS3839K33DBZR,Texas Instruments,C96333,,,,,,
"U5,U7",2,TPS2121RUXR,RUX0012A,TPS2121RUXR,Texas Instruments,C485916,,,https://www.ti.com/lit/gpn/tps2121,,,
U6,1,SN74AHCT1G08,SOT-23-5,SN74AHCT1G08DBVR,Texas Instruments,C113521,,,,,,
